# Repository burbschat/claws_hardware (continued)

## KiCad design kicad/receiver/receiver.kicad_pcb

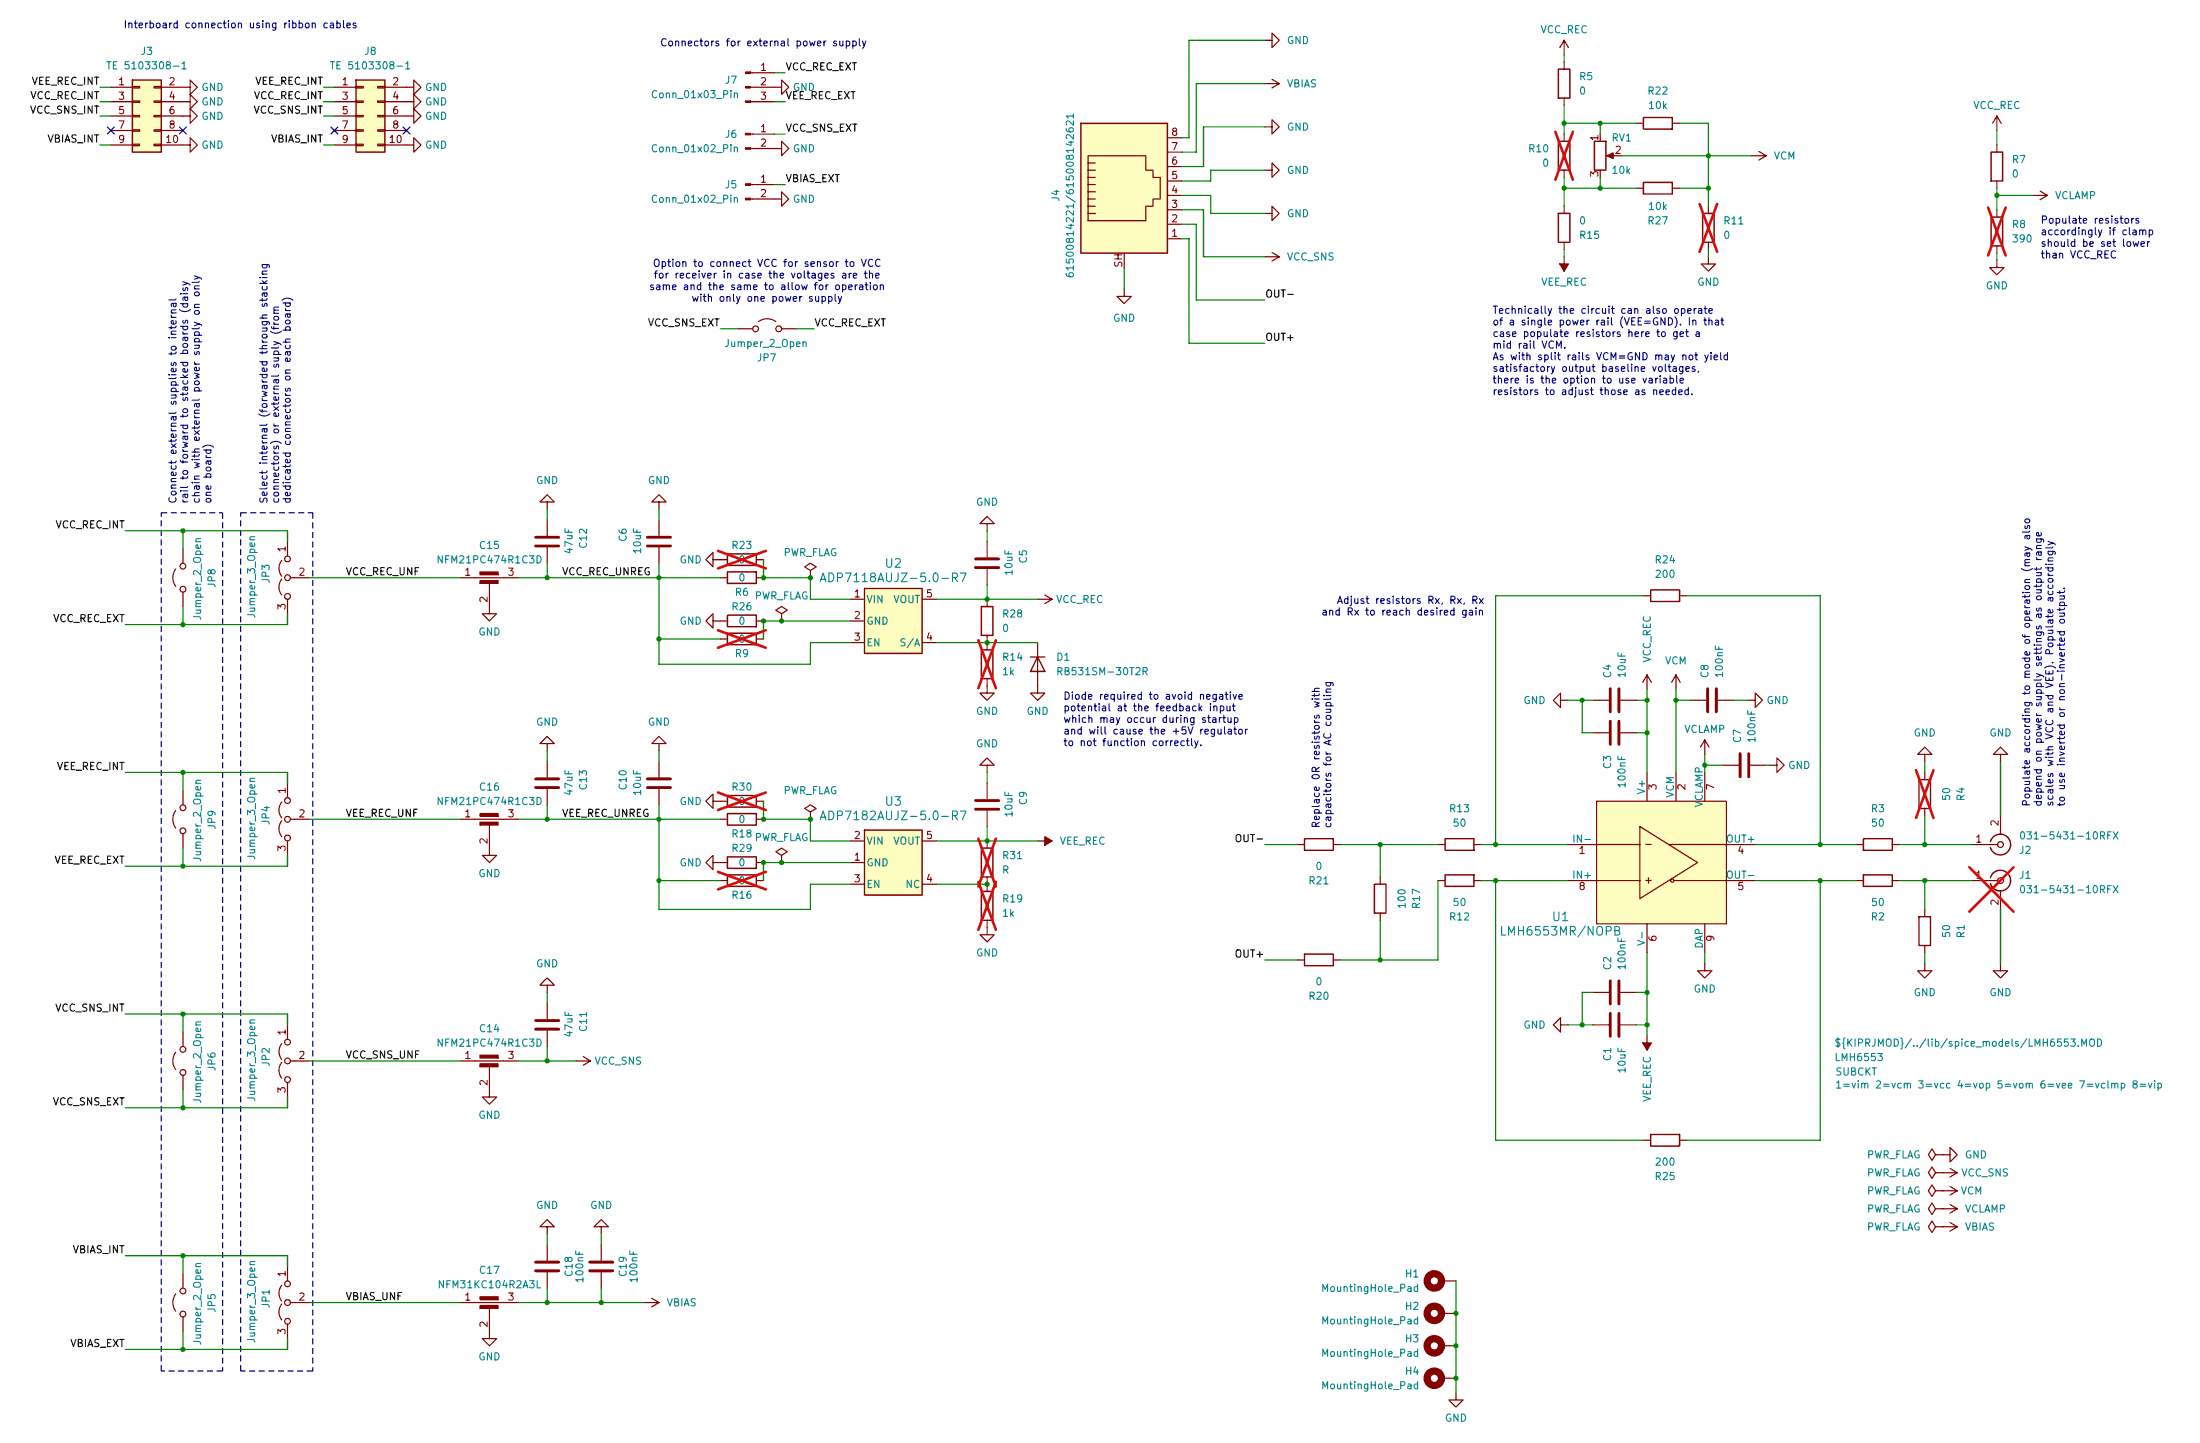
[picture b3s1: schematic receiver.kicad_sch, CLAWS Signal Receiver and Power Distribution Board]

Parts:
C1, C4, C5, C6, C9, C10: 10uF; C_0603_1608Metric; Part Number GRM188R61E106KA73D
C2, C3, C7, C8, C18, C19: 100nF; C_0603_1608Metric; Part Number GRM188R72A104KA35D
C11, C12, C13: 47uF; C_1210_3225Metric; Part Number GRM32EC81C476KE15K
C14, C15, C16: NFM21PC474R1C3D; NFM21PC225B0J3D_MUR; Part Number NFM21PC474R1C3D
C17: NFM31KC104R2A3L; NFM31KC104R2A3_MUR; Part Number NFM31KC104R2A3L
D1: RB531SM-30T2R; D_SOD-523; Part Number RB531SM-30T2R
H1, H2, H3, H4: MountingHole_Pad; MountingHole_3.2mm_M3_Pad_Via
J1: 031-5431-10RFX; BNC_Amphenol_031-5431-10RFX_Horizontal; Part Number 031-5431-10RFX; not fitted
J2: 031-5431-10RFX; BNC_Amphenol_031-5431-10RFX_Horizontal; Part Number 031-5431-10RFX
J3, J8: TE 5103308-1; PinHeader_2x05_P2.54mm_Vertical_Ribbon; Part Number 5103308-1
J4: 61500814221/615008142621; 61500814221_615008142621_hybrid; Part Number 61500814221
J5, J6: Conn_01x02_Pin; PhoenixContact_MC_1,5_2-G-3.81_1x02_P3.81mm_Horizontal; Part Number 1803277
J7: Conn_01x03_Pin; PhoenixContact_MC_1,5_3-G-3.81_1x03_P3.81mm_Horizontal; Part Number 1803280
JP1, JP2, JP3, JP4: Jumper_3_Open; PinHeader_1x03_P2.54mm_Vertical
JP5, JP6, JP7, JP8, JP9: Jumper_2_Open; PinHeader_1x02_P2.54mm_Vertical
R1, R2, R3, R12, R13: 50; R_0603_1608Metric; Part Number ERJ-3EKF49R9V
R4: 50; R_0603_1608Metric; Part Number ERJ-3EKF49R9V; not fitted
R5, R6, R7, R15, R18, R20, R21, R26, R28, R29: 0; R_0603_1608Metric; Part Number ERJ-3GEY0R00V
R8: 390; R_0603_1608Metric; not fitted
R9, R10, R11, R16, R23, R30: 0; R_0603_1608Metric; Part Number ERJ-3GEY0R00V; not fitted
R14, R19: 1k; R_0603_1608Metric; Part Number ERJ-3EKF1001V; not fitted
R17: 100; R_0603_1608Metric; Part Number ERJ-3EKF1000V
R22, R27: 10k; R_0603_1608Metric; Part Number ERJ-3EKF1002V
R24, R25: 200; R_0603_1608Metric; Part Number ERJ-3GEYJ201V
R31: R; R_0603_1608Metric; not fitted
RV1: 10k; Potentiometer_Bourns_3296X_Horizontal; Part Number 3296X-1-103LF
U1: LMH6553MR/NOPB; MRA08B; Part Number LMH6553MRE/NOPB
U2: ADP7118AUJZ-5.0-R7; TSOT-23-5; Part Number ADP7118AUJZ-5.0-R7
U3: ADP7182AUJZ-5.0-R7; TSOT-23-5; Part Number ADP7182AUJZ-5.0-R7

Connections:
/OUT+: J4.1, R20.2
/OUT-: J4.2, R21.1
/VBIAS_EXT: J5.1, JP1.3 (B), JP5.2 (B)
/VBIAS_INT: J3.9, J8.9, JP1.1 (A), JP5.1 (A)
/VBIAS_UNF: C17.1, JP1.2 (C)
/VCC_REC_EXT: J7.1, JP3.3 (B), JP7.1 (A), JP8.2 (B)
/VCC_REC_INT: J3.3, J8.3, JP3.1 (A), JP8.1 (A)
/VCC_REC_UNF: C15.1, JP3.2 (C)
/VCC_REC_UNREG: C6.1, C12.1, C15.3, R6.1, R9.1, U2.3 (EN)
/VCC_SNS_EXT: J6.1, JP2.3 (B), JP6.2 (B), JP7.2 (B)
/VCC_SNS_INT: J3.5, J8.5, JP2.1 (A), JP6.1 (A)
/VCC_SNS_UNF: C14.1, JP2.2 (C)
/VEE_REC_EXT: J7.3, JP4.3 (B), JP9.2 (B)
/VEE_REC_INT: J3.1, J8.1, JP4.1 (A), JP9.1 (A)
/VEE_REC_UNF: C16.1, JP4.2 (C)
/VEE_REC_UNREG: C10.1, C13.1, C16.3, R16.1, R18.1, U3.3 (EN)
GND: C1.2, C2.2, C3.2, C4.2, C5.2, C6.2, C7.1, C8.1, C9.2, C10.2, C11.2, C12.2, C13.2, C14.2, C15.2, C16.2, C17.2, C18.1, C19.1, D1.2 (A), H1.1, H2.1, H3.1, H4.1, J1.2 (Ext), J2.2 (Ext), J3.2, J3.4, J3.6, J3.10, J4.4, J4.5, J4.6, J4.8, J4.SH, J5.2, J6.2, J7.2, J8.2, J8.4, J8.6, J8.10, R1.1, R4.1, R8.2, R11.2, R14.2, R19.2, R23.1, R26.1, R29.1, R30.1, U1.9 (DAP)
unnamed: D1.1 (K), R14.1, R28.2, U2.4 (S/A)
unnamed: J1.1 (In), R1.2, R2.1
unnamed: J2.1 (In), R3.1, R4.2
unnamed: R5.2, R10.1, R22.1, RV1.1
unnamed: R10.2, R15.2, R27.1, RV1.3
unnamed: R12.1, R17.2, R20.1
unnamed: R13.1, R17.1, R21.2
unnamed: R12.2, R25.1, U1.8 (IN+)
unnamed: R13.2, R24.1, U1.1 (IN-)
unnamed: R3.2, R24.2, U1.4 (OUT+)
unnamed: R2.2, R25.2, U1.5 (OUT-)
unnamed: R9.2, R26.2, U2.2 (GND)
unnamed: R6.2, R23.2, U2.1 (VIN)
unnamed: R16.2, R29.2, U3.1 (GND)
unnamed: R19.1, R31.2, U3.4 (NC)
unnamed: R18.2, R30.2, U3.2 (VIN)
VBIAS: C17.3, C18.2, C19.2, J4.7
VCC_REC: C3.1, C4.1, C5.1, R5.1, R7.1, R28.1, U1.3 (V+), U2.5 (VOUT)
VCC_SNS: C11.1, C14.3, J4.3
VCLAMP: C7.2, R7.2, R8.1, U1.7 (VCLAMP)
VCM: C8.2, R11.1, R22.2, R27.2, RV1.2, U1.2 (VCM)
VEE_REC: C1.1, C2.1, C9.1, R15.1, R31.1, U1.6 (V-), U3.5 (VOUT)

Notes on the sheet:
Connect external supplies to internal rail to forward to stacked boards (daisy chain with external power supply on only one board)
Interboard connection using ribbon cables
Populate resistors accordingly if clamp should be set lower than VCC_REC
Select internal (forwarded through stacking connectors) or external suply (from dedicated connectors on each board)
Populate according to mode of operation (may also depend on power supply settings as output range scales with VCC and VEE). Populate accordingly to use inverted or non-inverted output.
Replace 0R resistors with capacitors for AC coupling
Technically the circuit can also operate of a single power rail (VEE=GND). In that case populate resistors here to get a mid rail VCM. As with split rails VCM=GND may not yield satisfactory output baseline voltages, there is the option to use variable resistors to adjust those as needed.
Connectors for external power supply
Diode required to avoid negative potential at the feedback input which may occur during startup and will cause the +5V regulator to not function correctly.
Adjust resistors Rx, Rx, Rx and Rx to reach desired gain
Option to connect VCC for sensor to VCC for receiver in case the voltages are the same and the same to allow for operation with only one power supply

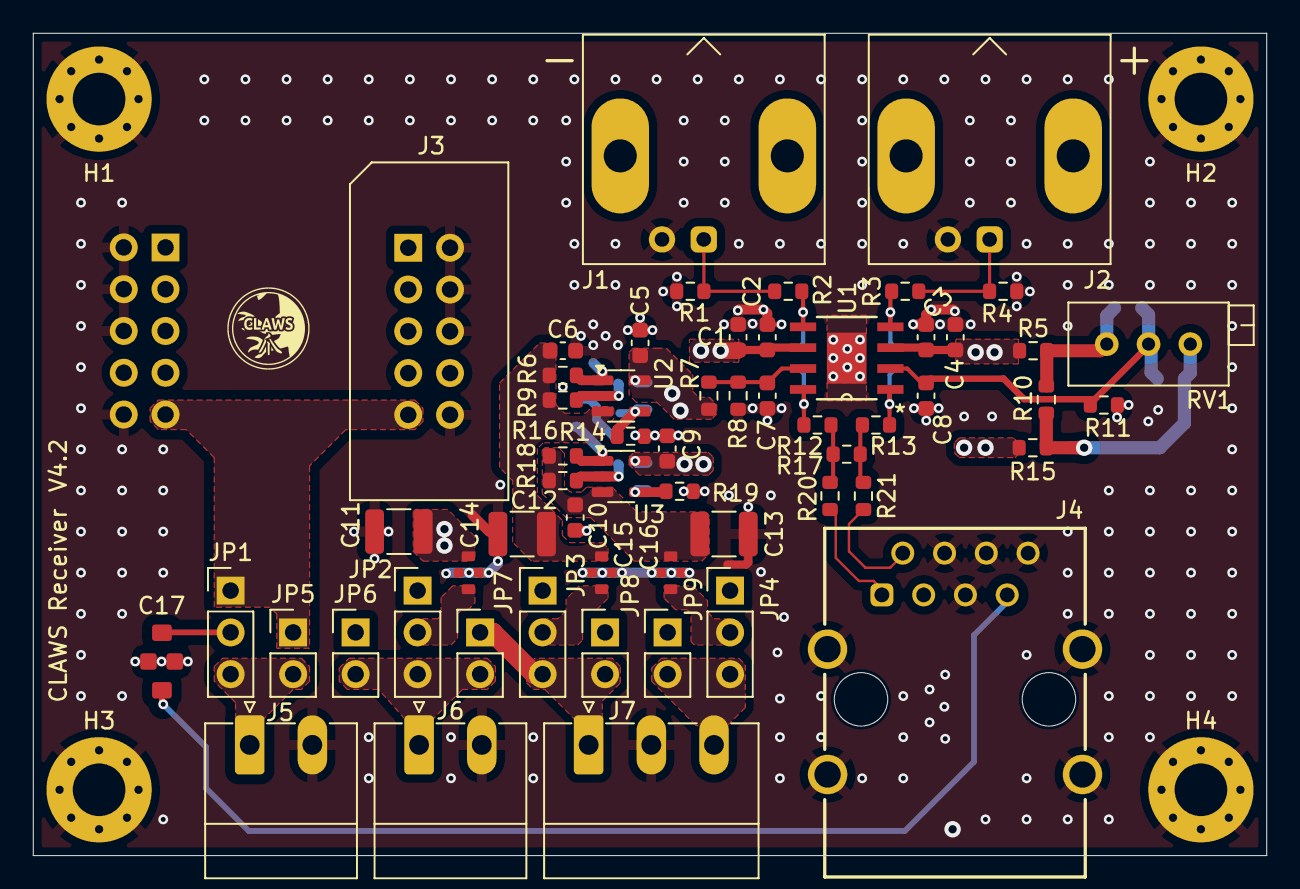
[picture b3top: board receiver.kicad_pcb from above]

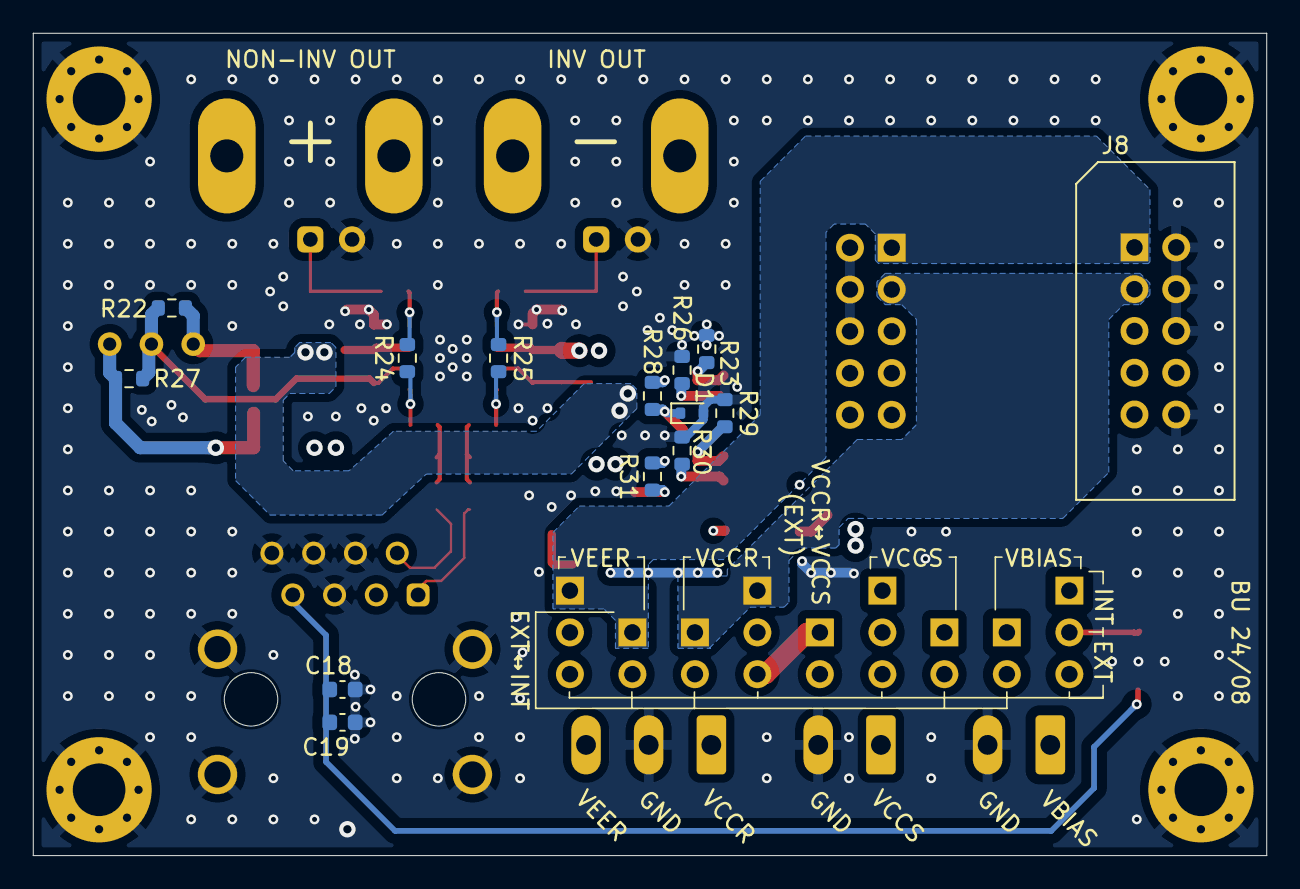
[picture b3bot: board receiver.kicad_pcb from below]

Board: 4 copper layers, 75.0 x 50.0 mm, 76 parts (14 on the bottom side), 39 nets.

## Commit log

2025-03-14 add note on state of this repo in readme
2025-04-27 Add license
2025-04-27 Add template file for manufacturer 'Unicraft'
2025-04-27 Add KiCad libraries and related 3d models
2025-04-27 Add top level gitignore
2025-04-27 Add KiCad project for receiver
2025-04-27 Add KiCad project for SiPM power supply
    Or a voltage supply if you prefer. It does not really provide much
    'power'.
2025-04-27 Add KiCad project for sensor
2025-04-27 Explain what is in this repository in the README
2025-07-04 Properly exclude tolerated DRC errors and fix silkscreen overlap
2025-07-04 Add github action to automatically add files from kibot to release
